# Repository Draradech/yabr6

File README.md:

# yabr6
Yet another balancing robot (generation 6). ESP32, stepper motors.

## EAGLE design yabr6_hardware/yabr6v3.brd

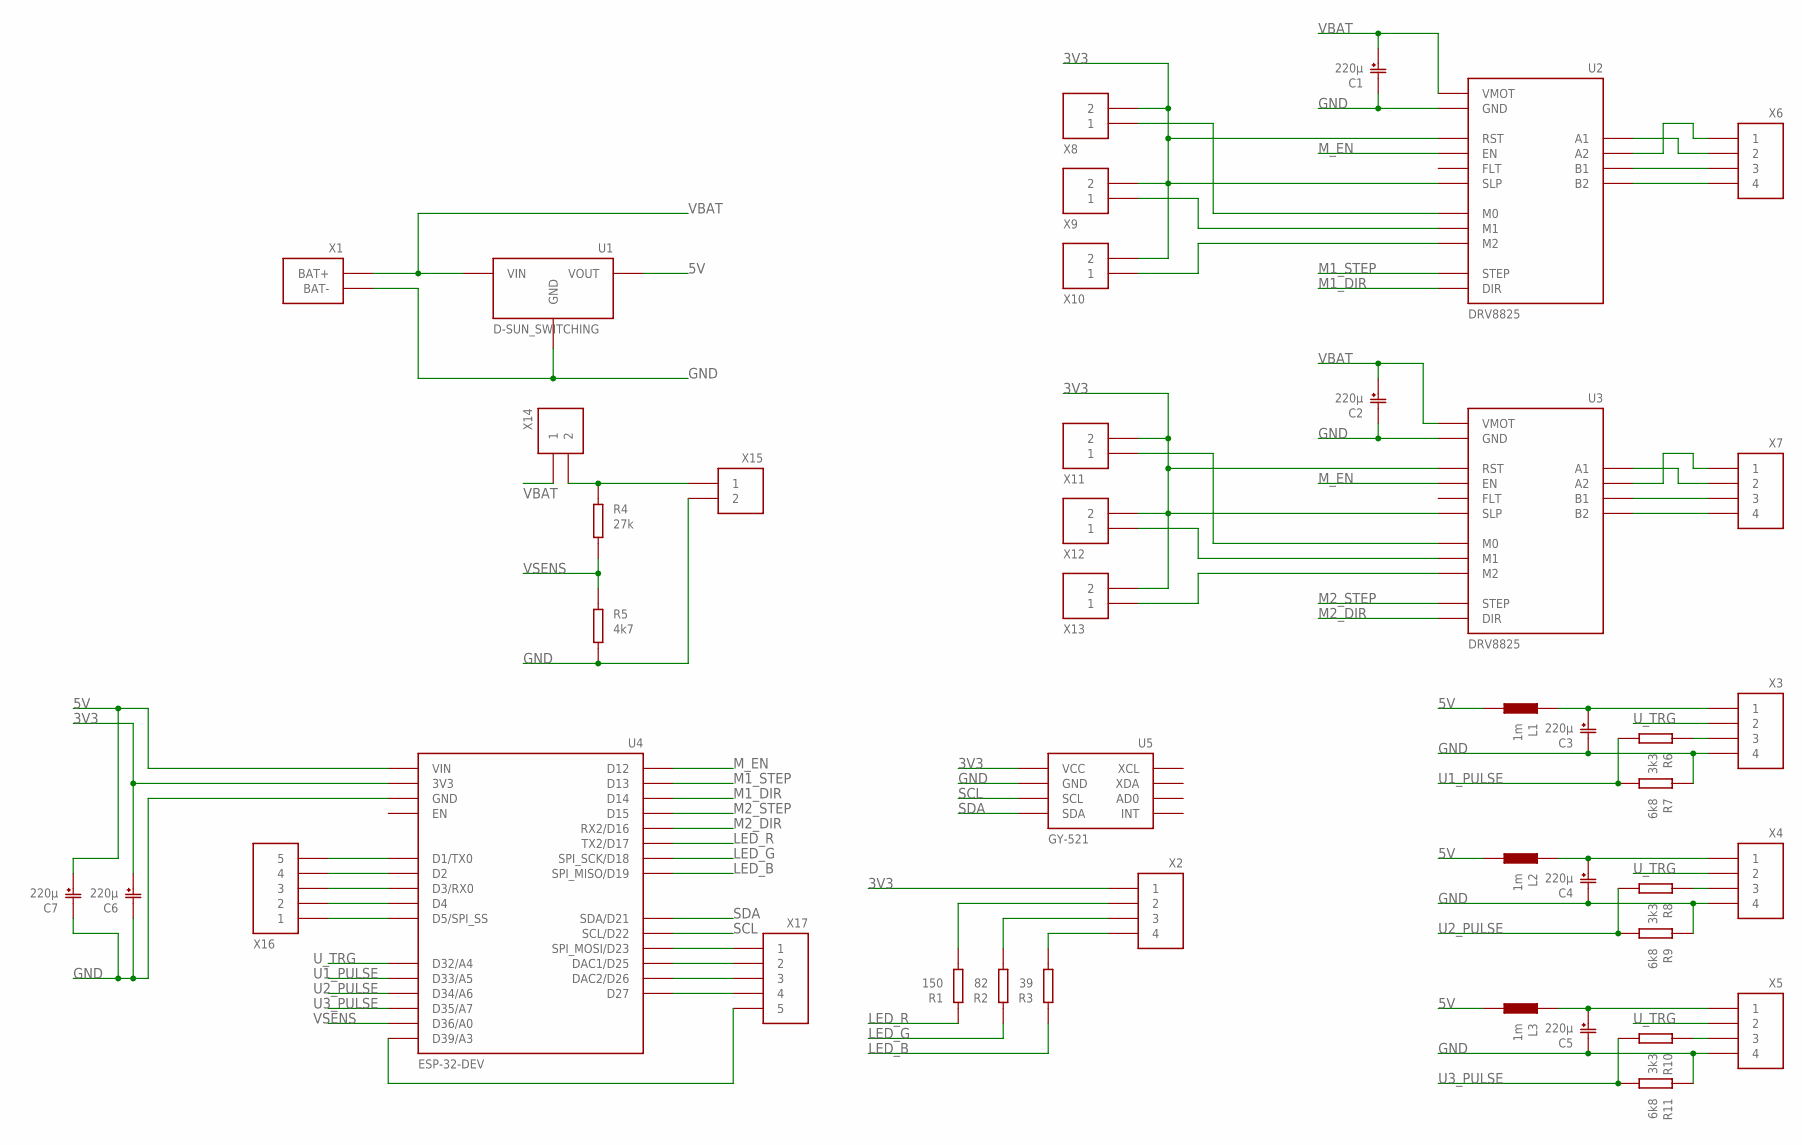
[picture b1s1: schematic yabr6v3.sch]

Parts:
C1, C2, C3, C4, C5, C6, C7: 220µ; CPOL_3,5
L1, L2, L3: 1m; NEOSID_SD75
R1: 150; R_12
R2: 82; R_12
R3: 39; R_12
R4: 27k; R_12
R5: 4k7; R_12
R6, R8, R10: 3k3; R_12
R7, R9, R11: 6k8; R_12
U1: D-SUN_SWITCHING
U2, U3: DRV8825
U4: ESP-32-DEV
U5: GY-521
X1: BAT
X2, X3, X4, X5, X6, X7: X4
X8, X9, X10, X11, X12, X13, X14, X15: X2
X16, X17: X5

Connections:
3V3: C6.P (+), U2.P$11 (SLP), U2.P$12 (RST), U3.P$11 (SLP), U3.P$12 (RST), U4.P$15 (3V3), U5.P$8 (VCC), X2.P$1 (1), X8.P$2 (2), X9.P$2 (2), X10.P$2 (2), X11.P$2 (2), X12.P$2 (2), X13.P$2 (2)
5V: C7.P (+), L1.P, L2.P, L3.P, U1.PO (VOUT), U1.PO2 (VOUT), U4.P$16 (VIN)
GND: C1.N (-), C2.N (-), C3.N (-), C4.N (-), C5.N (-), C6.N (-), C7.N (-), R5.P, R7.N, R9.N, R11.N, U1.NI (GND), U1.NI2 (GND), U1.NO (GND), U1.NO2 (GND), U2.P$2 (GND), U2.P$8 (GND), U3.P$2 (GND), U3.P$8 (GND), U4.P$14 (GND), U4.P$17 (GND), U5.P$7 (GND), X1.N (BAT-), X3.P$4 (4), X4.P$4 (4), X5.P$4 (4), X15.P$2 (2)
LED_B: R3.N, U4.P$6 (SPI_MISO/D19)
LED_G: R2.N, U4.P$7 (SPI_SCK/D18)
LED_R: R1.N, U4.P$9 (TX2/D17)
M1_DIR: U2.P$9 (DIR), U4.P$20 (D14)
M1_STEP: U2.P$10 (STEP), U4.P$18 (D13)
M2_DIR: U3.P$9 (DIR), U4.P$10 (RX2/D16)
M2_STEP: U3.P$10 (STEP), U4.P$13 (D15)
M_EN: U2.P$16 (EN), U3.P$16 (EN), U4.P$19 (D12)
unnamed: U2.P$5 (A1), X6.P$2 (2)
unnamed: U2.P$6 (A2), X6.P$1 (1)
unnamed: U2.P$4 (B1), X6.P$3 (3)
unnamed: U2.P$3 (B2), X6.P$4 (4)
unnamed: U3.P$5 (A1), X7.P$2 (2)
unnamed: U3.P$6 (A2), X7.P$1 (1)
unnamed: U3.P$4 (B1), X7.P$3 (3)
unnamed: U3.P$3 (B2), X7.P$4 (4)
unnamed: U2.P$15 (M0), X8.P$1 (1)
unnamed: U2.P$14 (M1), X9.P$1 (1)
unnamed: U2.P$13 (M2), X10.P$1 (1)
unnamed: U3.P$15 (M0), X11.P$1 (1)
unnamed: U3.P$14 (M1), X12.P$1 (1)
unnamed: U3.P$13 (M2), X13.P$1 (1)
unnamed: C3.P (+), L1.N, X3.P$1 (1)
unnamed: R3.P, X2.P$4 (4)
unnamed: R2.P, X2.P$3 (3)
unnamed: C4.P (+), L2.N, X4.P$1 (1)
unnamed: R6.N, X3.P$3 (3)
unnamed: R4.N, X14.P$2 (2), X15.P$1 (1)
unnamed: C5.P (+), L3.N, X5.P$1 (1)
unnamed: R8.N, X4.P$3 (3)
unnamed: R1.P, X2.P$2 (2)
unnamed: U4.P$8 (D5/SPI_SS), X16.P$1 (1)
unnamed: R10.N, X5.P$3 (3)
unnamed: U4.P$11 (D4), X16.P$2 (2)
unnamed: U4.P$4 (D3/RX0), X16.P$3 (3)
unnamed: U4.P$12 (D2), X16.P$4 (4)
unnamed: U4.P$3 (D1/TX0), X16.P$5 (5)
unnamed: U4.P$1 (SPI_MOSI/D23), X17.P$1 (1)
unnamed: U4.P$23 (DAC1/D25), X17.P$2 (2)
unnamed: U4.P$22 (DAC2/D26), X17.P$3 (3)
unnamed: U4.P$21 (D27), X17.P$4 (4)
unnamed: U4.P$28 (D39/A3), X17.P$5 (5)
SCL: U4.P$2 (SCL/D22), U5.P$6 (SCL)
SDA: U4.P$5 (SDA/D21), U5.P$5 (SDA)
U1_PULSE: R6.P, R7.P, U4.P$24 (D33/A5)
U2_PULSE: R8.P, R9.P, U4.P$27 (D34/A6)
U3_PULSE: R10.P, R11.P, U4.P$26 (D35/A7)
U_TRG: U4.P$25 (D32/A4), X3.P$2 (2), X4.P$2 (2), X5.P$2 (2)
VBAT: C1.P (+), C2.P (+), U1.PI (VIN), U1.PI2 (VIN), U2.P$1 (VMOT), U3.P$1 (VMOT), X1.P (BAT+), X14.P$1 (1)
VSENS: R4.P, R5.N, U4.P$29 (D36/A0)

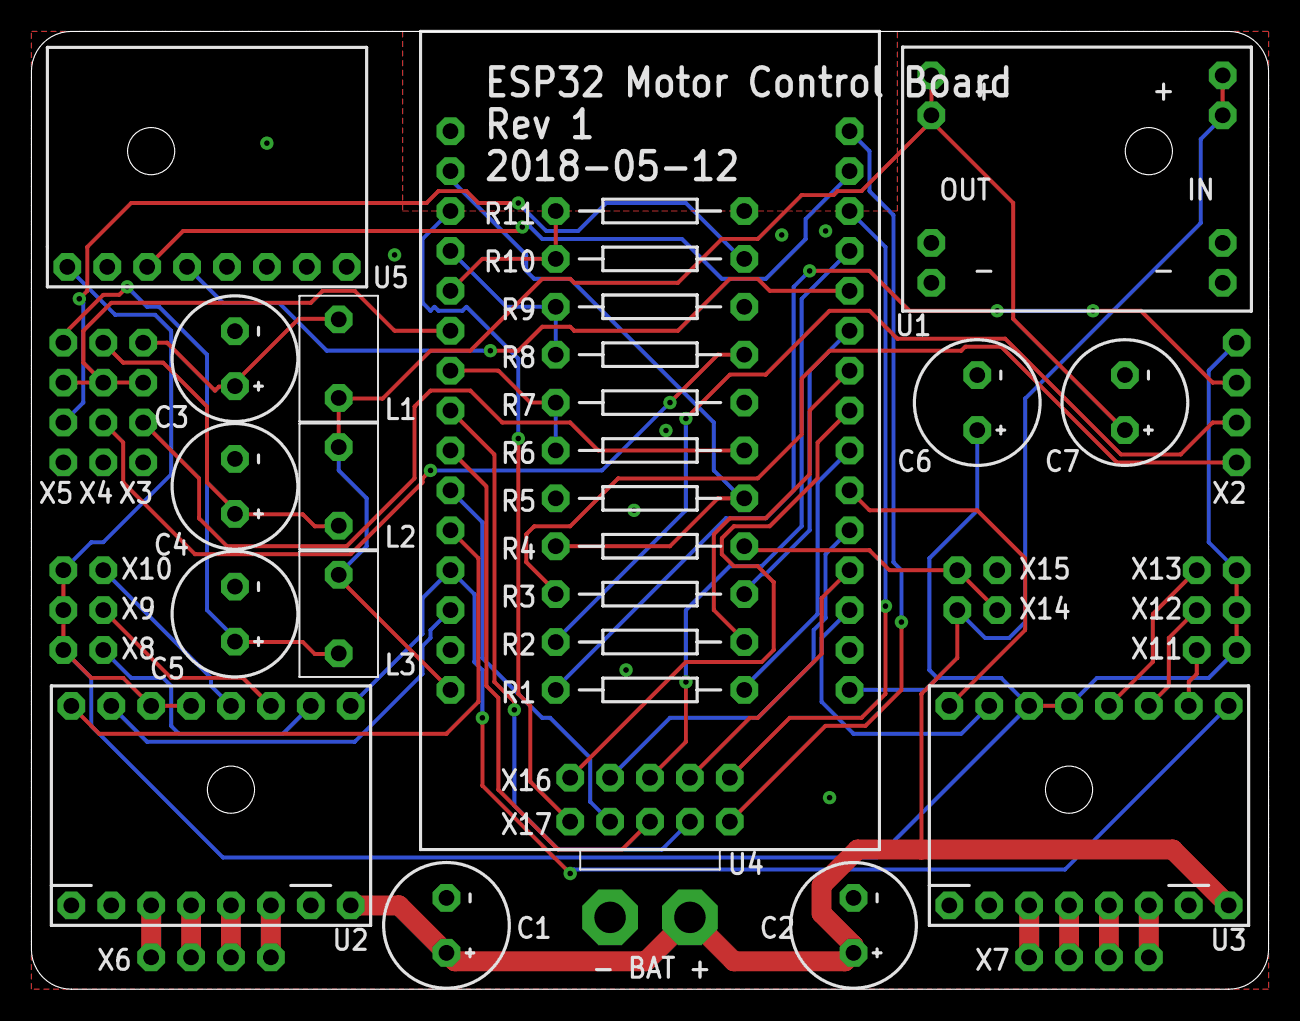
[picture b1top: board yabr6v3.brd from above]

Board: 2 copper layers, 78.7 x 61.0 mm, 43 parts (0 on the bottom side), 53 nets.

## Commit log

2018-10-06 working version
2018-10-07 optimizations
2018-10-11 add 3d model and cut exports
